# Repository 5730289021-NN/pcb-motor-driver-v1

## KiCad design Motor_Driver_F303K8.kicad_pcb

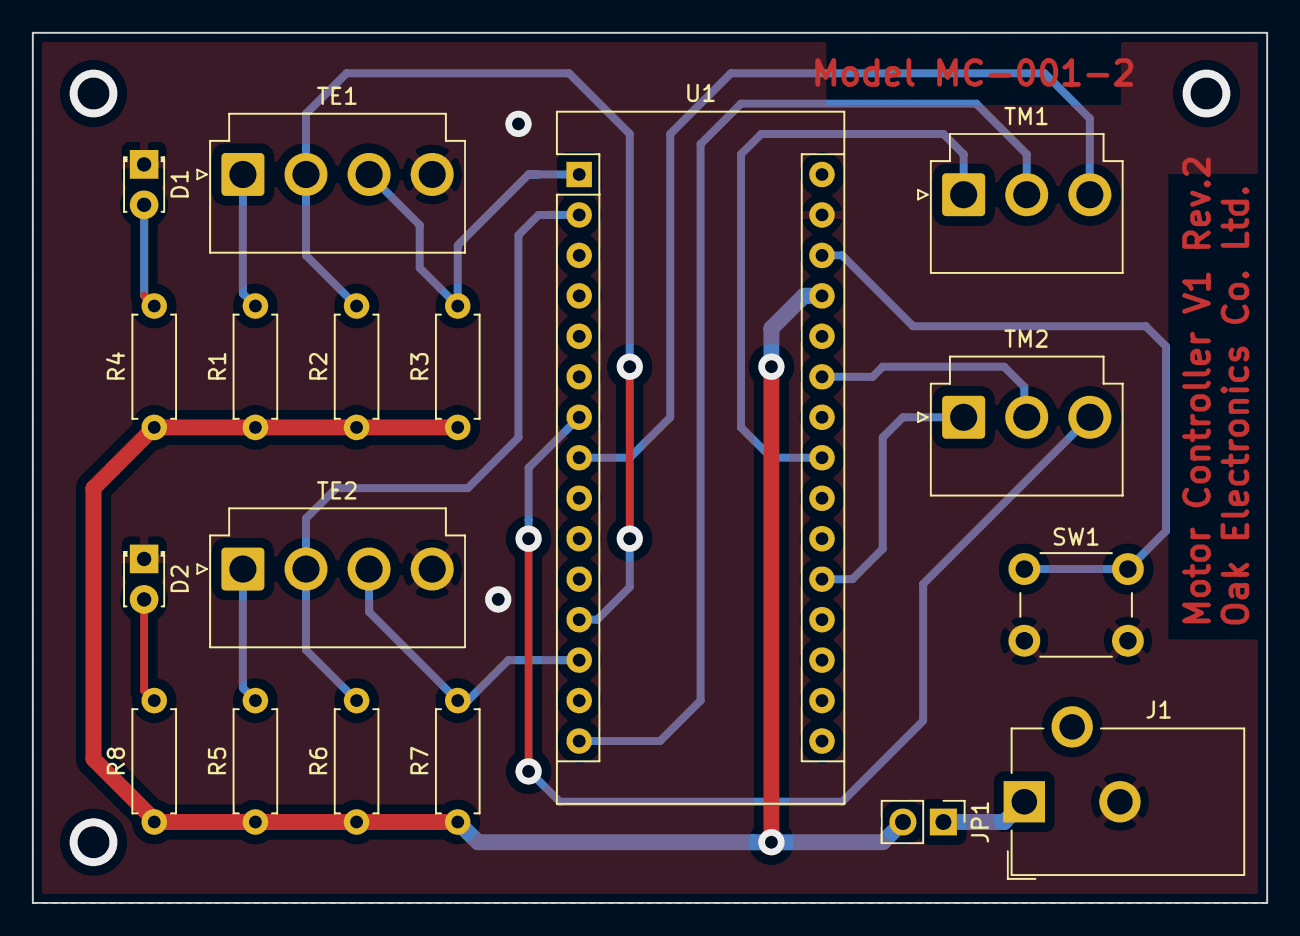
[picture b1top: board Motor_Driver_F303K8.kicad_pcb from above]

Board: 2 copper layers, 77.5 x 54.6 mm, 18 parts (0 on the bottom side), 18 nets.

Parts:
D1, D2: LED; LED_D1.8mm_W3.3mm_H2.4mm
J1: Barrel_Jack; BarrelJack_CUI_PJ-102AH_Horizontal
JP1: Jumper_2_Open; PinHeader_1x02_P2.54mm_Vertical
R1, R5: 220; R_Axial_DIN0207_L6.3mm_D2.5mm_P7.62mm_Horizontal
R2, R3, R6, R7: 8k2; R_Axial_DIN0207_L6.3mm_D2.5mm_P7.62mm_Horizontal
R4, R8: 1k; R_Axial_DIN0207_L6.3mm_D2.5mm_P7.62mm_Horizontal
SW1: SW_Push; SW_PUSH_6mm_H7.3mm
TE1, TE2: Conn_01x04_Male; JST_VH_B4P-VH_1x04_P3.96mm_Vertical
TM1, TM2: Conn_01x03_Male; JST_VH_B3P-VH_1x03_P3.96mm_Vertical
U1: NUCLEO32-F303K8; Arduino_Nano

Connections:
1A: R2.2, TE1.2, U1.12
1B: R3.2, TE1.3, U1.1
2A: R6.2, TE2.2, U1.2
2B: R7.2, TE2.3, U1.13
+5V: J1.1, JP1.1
ENA: TM1.1, U1.23
ENB: TM2.1, U1.20
GND: D1.1, D2.1, J1.2, SW1.2, TE1.4, TE2.4, U1.29
IN1: TM1.2, U1.15
IN2: TM1.3, U1.8
IN3: TM2.2, U1.25
IN4: TM2.3, U1.7
unnamed: D1.2, R4.2
unnamed: D2.2, R8.2
unnamed: R1.2, TE1.1
unnamed: R5.2, TE2.1
RST: SW1.1, U1.28
VCC: JP1.2, R1.1, R2.1, R3.1, R4.1, R5.1, R6.1, R7.1, R8.1, U1.27

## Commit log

2020-06-08 add files
